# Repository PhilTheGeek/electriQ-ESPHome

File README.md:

# electriQ-ESPHome

## Background

I bought a number of these electriQ minisplit air conditioners and they work fine with the in-built wifi module and its Tuya integration into Home Assistant.  But I prefer to use on-premises solutions that don't rely on cloud, especially when that cloud is Chinese owned. A bit of reverse engineering of the Tuya datapoints led to this design.

The electriQ brand is, as far as I can tell, a UK specific brand that is put onto more generic Chinese products.  If your board looks like these then it might also work.

Front of the original board:

Back of the original board:

## Bill of Materials

| Part | Part Number |
| ---- | ----------- |
| R1 | 10k 0603 |
| R2 | 10k 0603 |
| R3 | 100R 0603 |
| R4 | 10k 0603 |
| R5 | 10k 0603 |
| R6 | 100R 0603 |
| U1 | ESP32-C3 SuperMini (must be one with onboard flash)|
| J1 | S4B-PH-K-S |

## ESPHome

Use the example YAML, amending entries with {} tags.  If your unit has horizontal swing then uncomment the 107 datapoint.  
There are 3 bitmask bytes which I've left in. I've never seen them change. Data point 108 is always 0xFF, 109 0x00 and 110 0x00.  Please let me know if you find out if they change and why.  

## New board

Gerbers in the gerber folder and the board will end up looking a bit like this (I've rotated Q2 and R4 to align with the other components since building this board). I added the JST connector for ease but the solder header could be transferred from the original board.

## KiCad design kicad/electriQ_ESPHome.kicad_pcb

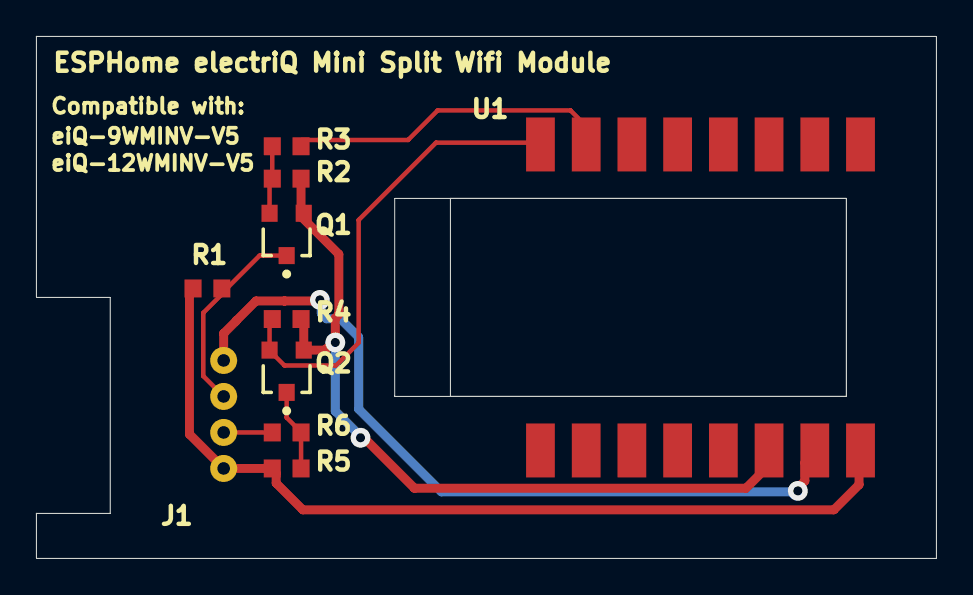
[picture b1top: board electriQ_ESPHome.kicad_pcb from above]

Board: 2 copper layers, 50.0 x 29.0 mm, 10 parts (0 on the bottom side), 9 nets.

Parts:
J1: S4B-PH-K-S; s4b-ph-k-s
Q1, Q2: BSS138; SOT23
R1, R2, R4, R5: 10k; ERA-0603
R3, R6: 100R; ERA-0603
U1: ESP32-C3 SuperMini

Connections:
+5: J1.4, R1.2, R5.2, U1.16
GND: J1.1, U1.15
NetQ1_2: Q1.2, R2.1, R3.1
NetQ2_1: Q2.1, R5.1, R6.2
RXD: J1.2, Q1.1, R1.1
RXD_3V3: R3.2, U1.7
TXD: J1.3, R6.1
TXD_3V3: Q2.2, R4.1, U1.8
VCC: Q1.3, Q2.3, R2.2, R4.2, U1.14

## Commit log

2025-12-08 Minor update to yaml
